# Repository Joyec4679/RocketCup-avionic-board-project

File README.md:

# 🚀 RocketCup Avionic Board Project (成大 ISP 航電組)

歡迎來到成大 ISP 航電組的協作平台！這裡存放了我們為比賽設計的所有電路圖與 PCB 檔案。

因為大家都是第一次使用 GitHub，請**務必**仔細閱讀以下的操作指南，以避免檔案衝突或覆蓋掉別人的心血。

---

## 📂 檔案結構說明 (去哪裡找你的檔案？)

我們採用分工合作的資料夾結構，請在自己的負責區域內工作：

* **`BigAvionic/`**: 大火箭航電板專區
* **`SmallAvionic/`**: 小火箭航電板專區
* **`Lib/`**: 共用的零件庫 (Symbol & Footprint)

> ⚠️ **重要原則**：除非你要修改共用零件庫，否則請盡量專注在自己負責的資料夾內，避免動到別組的檔案。

---

## ⚡ 每日開發流程 (SOP)

為了避免「悲劇」（檔案衝突），請大家養成習慣，每次開工前都要唸一遍口訣：**「先拉，再做，後推」**。

### 1️⃣ 開工第一件事：拉取 (Pull)
**只要你剛坐下準備開始畫圖，不管你覺得有沒有人改過，請先執行：**
```bash
git pull origin main

```

* **為什麼？** 這是把雲端最新的進度同步到你的電腦。如果你不拉就開始改，最後上傳時會發生衝突。

### 2️⃣ 進行開發

* 打開 KiCad，編輯你的電路圖或 PCB。
* 記得隨時存檔 (Ctrl+S)。

### 3️⃣ 收工上傳三步曲：加、存、推

當你完成一個階段的工作（例如：畫完電源線、放完電容），請依序執行：

**Step A: 加入變更 (Add)**
告訴 Git 這一輪你要上傳哪些檔案。

```bash
git add .

```

**Step B: 提交紀錄 (Commit)**
寫下你到底改了什麼。
！！！絕對不要有啥都沒有描述的commit！！！

```bash
git commit -m "清楚的描述，例如：完成 RocketCom 的 3.3V 電源佈線"

```

**Step C: 推送到雲端 (Push)**
這一步才是真的傳到 GitHub 上。

```bash
git push origin main

```

---

## 💣 KiCad 協作特別注意事項 (必讀！)

### 1. 關於 PCB 檔案 (`.kicad_pcb`)

Git 很擅長合併程式碼，但**非常不擅長合併 PCB 檔**。

* **黃金法則**：同一時間，**只能有一個人**修改同一張 PCB 板。
* **溝通**：要改 Layout 之前，請在群組喊一聲：「我要改通訊板的 PCB 囉！」，確認沒人正在改再動手。

---

## ❓ 常見問題救生圈

### Q1: 我輸入 `git push` 時出現 `error: failed to push some refs...` 怎麼辦？

這代表有人在你工作的時候，已經先上傳了新版本。
**解法：**

1. 先輸入 `git pull origin main` (把對方的東西抓下來合併)。
2. 如果不幸出現衝突 (Conflict)，請找組長求救。
3. 合併成功後，再輸入一次 `git push origin main`。

### Q2: 為什麼有些備份檔 (`.bak`) 傳不上去？

這是正常的！我們設定了 `.gitignore` 來過濾掉那些垃圾檔案，保持專案乾淨。請不要強行上傳它們。

---

### 🔧 環境設定檢查

* **KiCad 版本**：請大家統一使用 **KiCad 7.0** ，避免檔案格式跑掉。
* **Git 設定**：第一次使用請設定你的名字和 Email：
```bash
git config --global user.name "你的名字(英文)"
git config --global user.email "你的Email"
```

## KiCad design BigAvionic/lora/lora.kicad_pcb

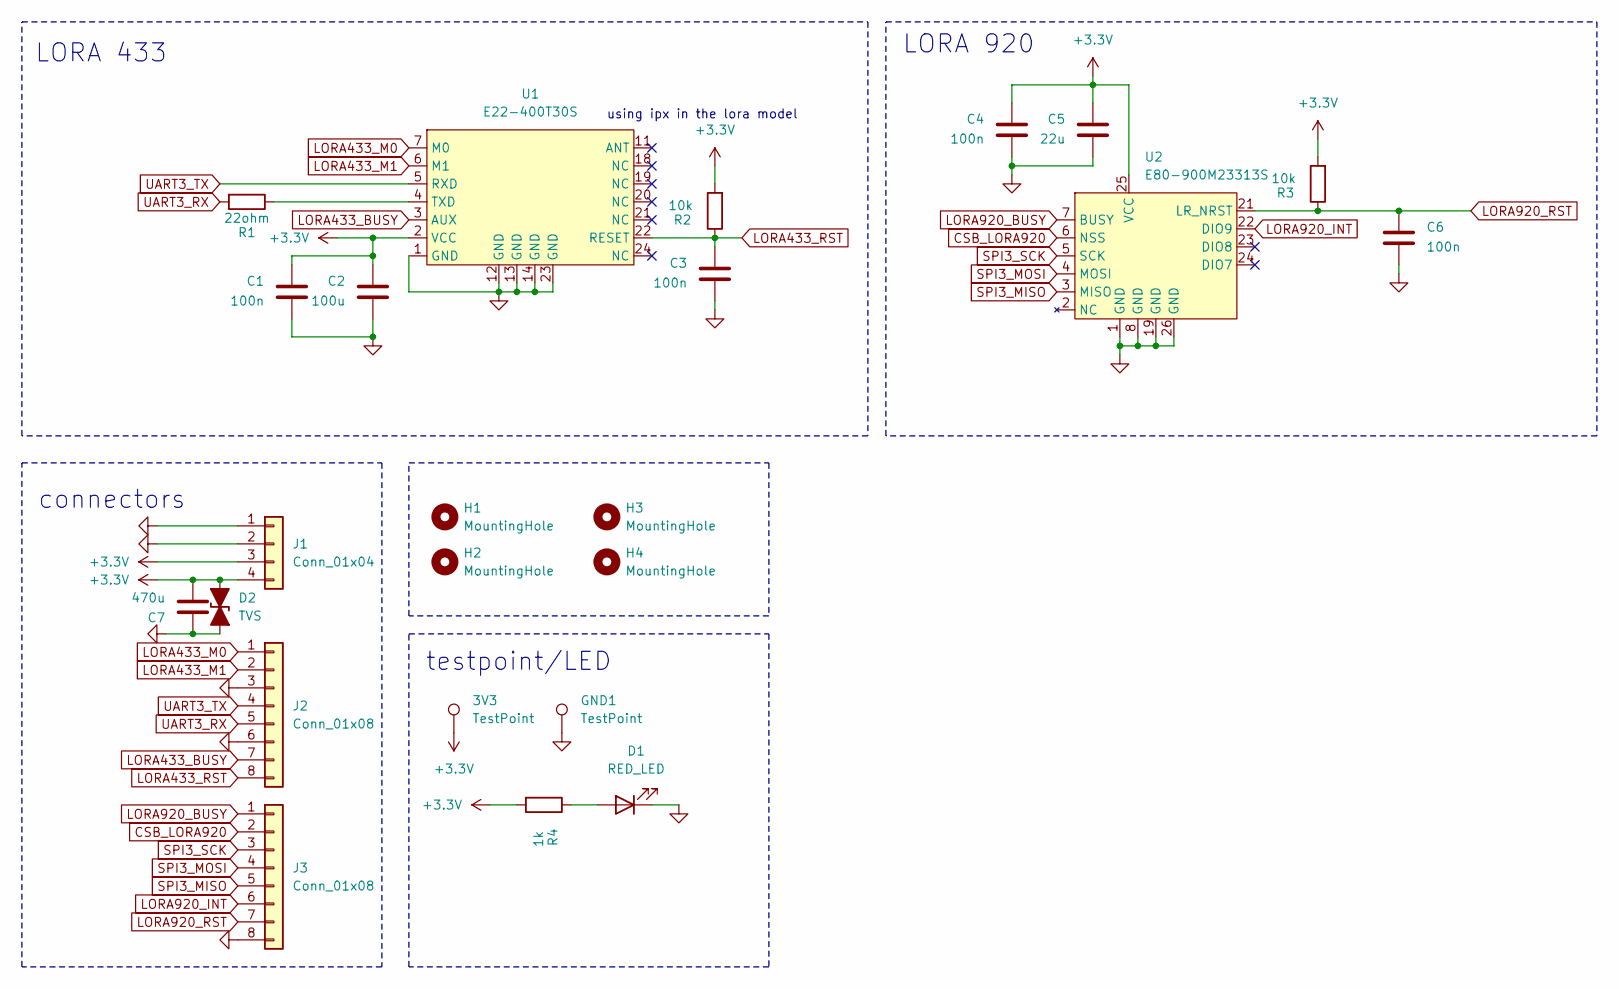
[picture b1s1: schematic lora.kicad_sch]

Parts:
3V3: TestPoint; TestPoint_Pad_D1.0mm
C1, C3, C4, C6: 100n; C_0805_2012Metric_Pad1.18x1.45mm_HandSolder
C2: 100u; CP_EIA-7343-31_Kemet-D_HandSolder
C5: 22u; C_1206_3216Metric_Pad1.33x1.80mm_HandSolder
C7: 470u; CP_EIA-7343-43_Kemet-X_HandSolder
D1: RED_LED; LED_0805_2012Metric_Pad1.15x1.40mm_HandSolder
D2: TVS; D_SMA
GND1: TestPoint; TestPoint_Pad_D1.0mm
H1, H2, H3, H4: MountingHole; MountingHole_3.2mm_M3_DIN965_Pad
J1: Conn_01x04; JST_GH_SM04B-GHS-TB_1x04-1MP_P1.25mm_Horizontal
J2, J3: Conn_01x08; JST_GH_SM08B-GHS-TB_1x08-1MP_P1.25mm_Horizontal
R1: 22ohm; R_0805_2012Metric_Pad1.20x1.40mm_HandSolder
R2, R3: 10k; R_0805_2012Metric_Pad1.20x1.40mm_HandSolder
R4: 1k; R_0805_2012Metric_Pad1.20x1.40mm_HandSolder
U1: E22-400T30S; XCVR_E22-900T30S
U2: E80-900M23313S; E80-xxxM2213S

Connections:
+3.3V: 3V3.1, C1.1, C2.1, C4.1, C5.1, C7.2, D2.2 (A2), J1.3, J1.4, R2.2, R3.2, R4.2, U1.2 (VCC), U2.25 (VCC)
CSB_LORA920: J3.2, U2.6 (NSS)
GND: C1.2, C2.2, C3.2, C4.2, C5.2, C6.2, C7.1, D1.1 (K), D2.1 (A1), GND1.1, J1.1, J1.2, J2.3, J2.6, J3.8, U1.1 (GND), U1.12 (GND), U1.13 (GND), U1.14 (GND), U1.23 (GND), U2.1 (GND), U2.8 (GND), U2.19 (GND), U2.26 (GND)
LORA433_BUSY: J2.7, U1.3 (AUX)
LORA433_M0: J2.1, U1.7 (M0)
LORA433_M1: J2.2, U1.6 (M1)
LORA433_RST: C3.1, J2.8, R2.1, U1.22 (RESET)
LORA920_BUSY: J3.1, U2.7 (BUSY)
LORA920_INT: J3.6, U2.22 (DIO9)
LORA920_RST: C6.1, J3.7, R3.1, U2.21 (LR_NRST)
unnamed: D1.2 (A), R4.1
unnamed: R1.1, U1.4 (TXD)
SPI3_MISO: J3.5, U2.3 (MISO)
SPI3_MOSI: J3.4, U2.4 (MOSI)
SPI3_SCK: J3.3, U2.5 (SCK)
UART3_RX: J2.5, R1.2
UART3_TX: J2.4, U1.5 (RXD)

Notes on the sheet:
LORA 920
testpoint/LED
using ipx in the lora model
connectors
LORA 433

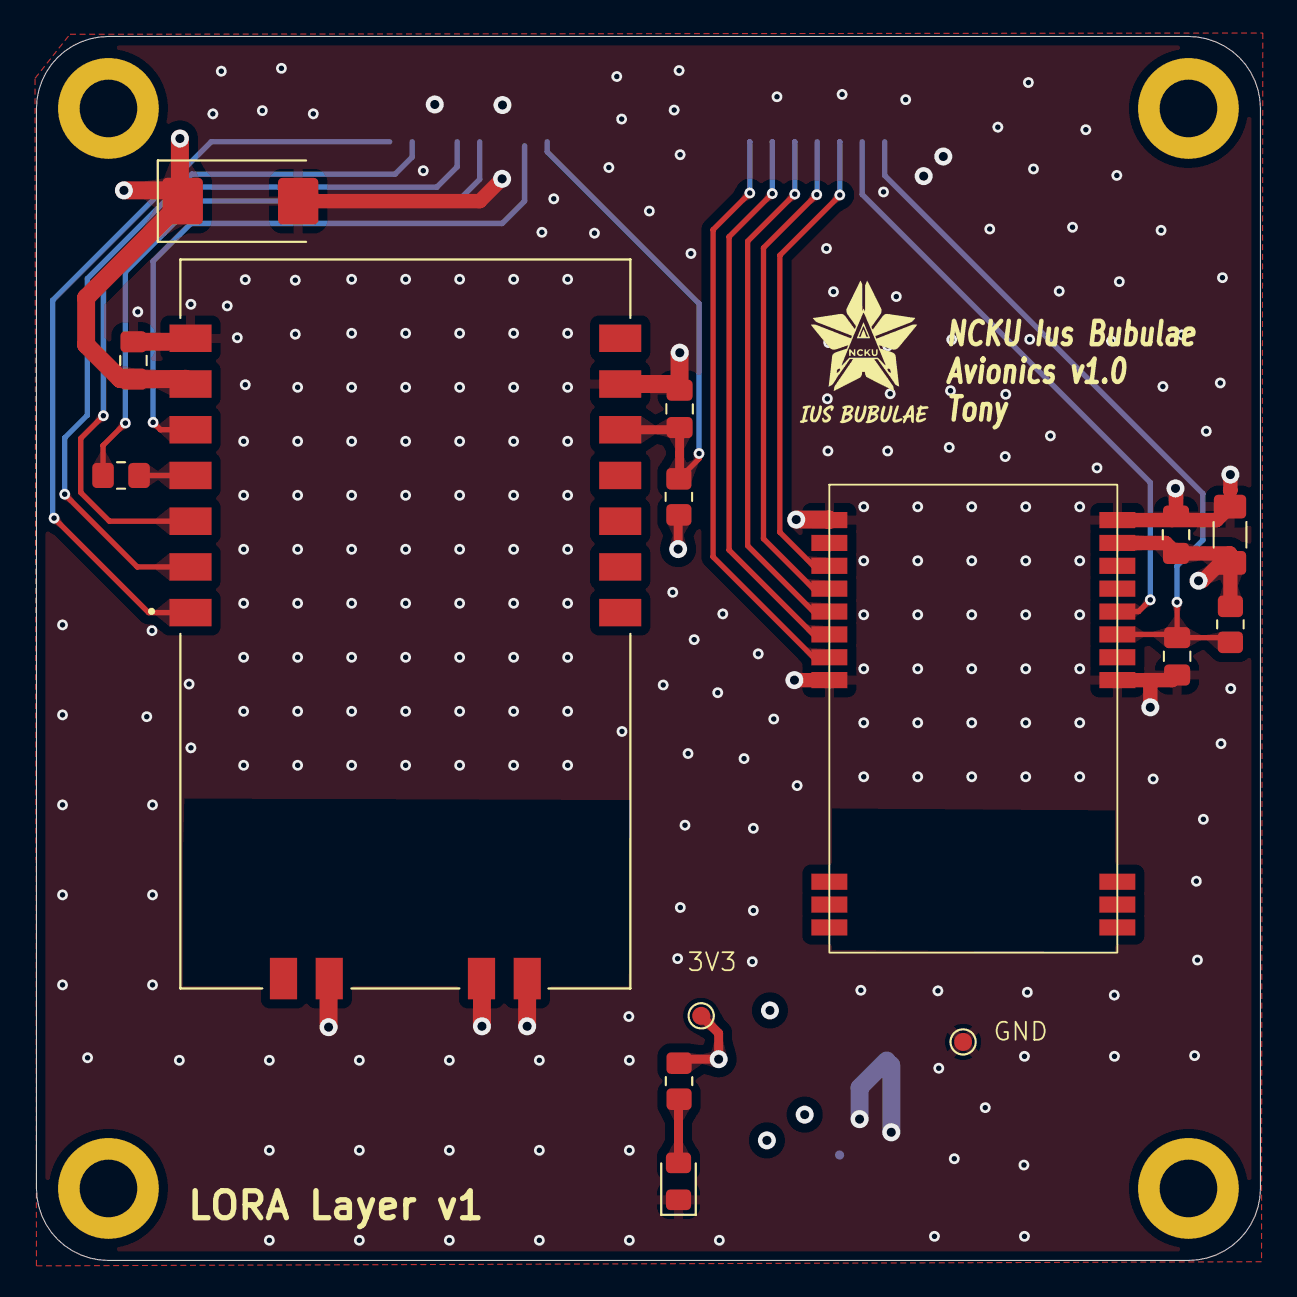
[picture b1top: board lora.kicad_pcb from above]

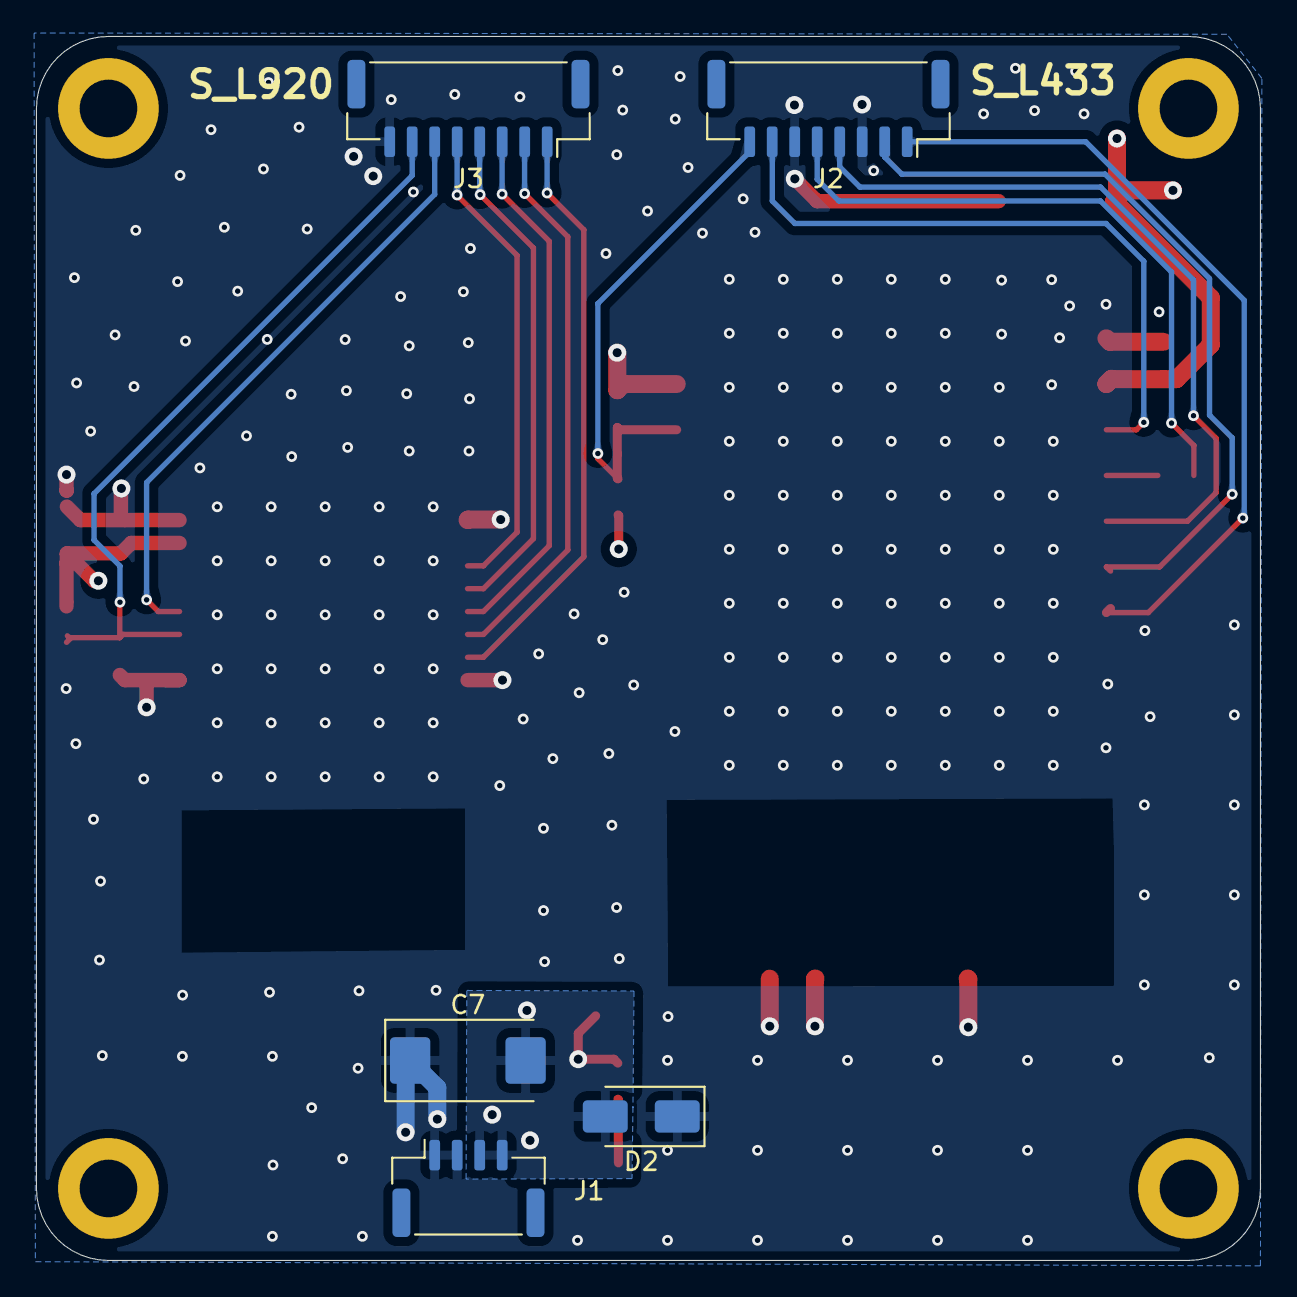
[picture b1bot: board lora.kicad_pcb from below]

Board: 4 copper layers, 68.0 x 68.0 mm, 24 parts (5 on the bottom side), 17 nets.

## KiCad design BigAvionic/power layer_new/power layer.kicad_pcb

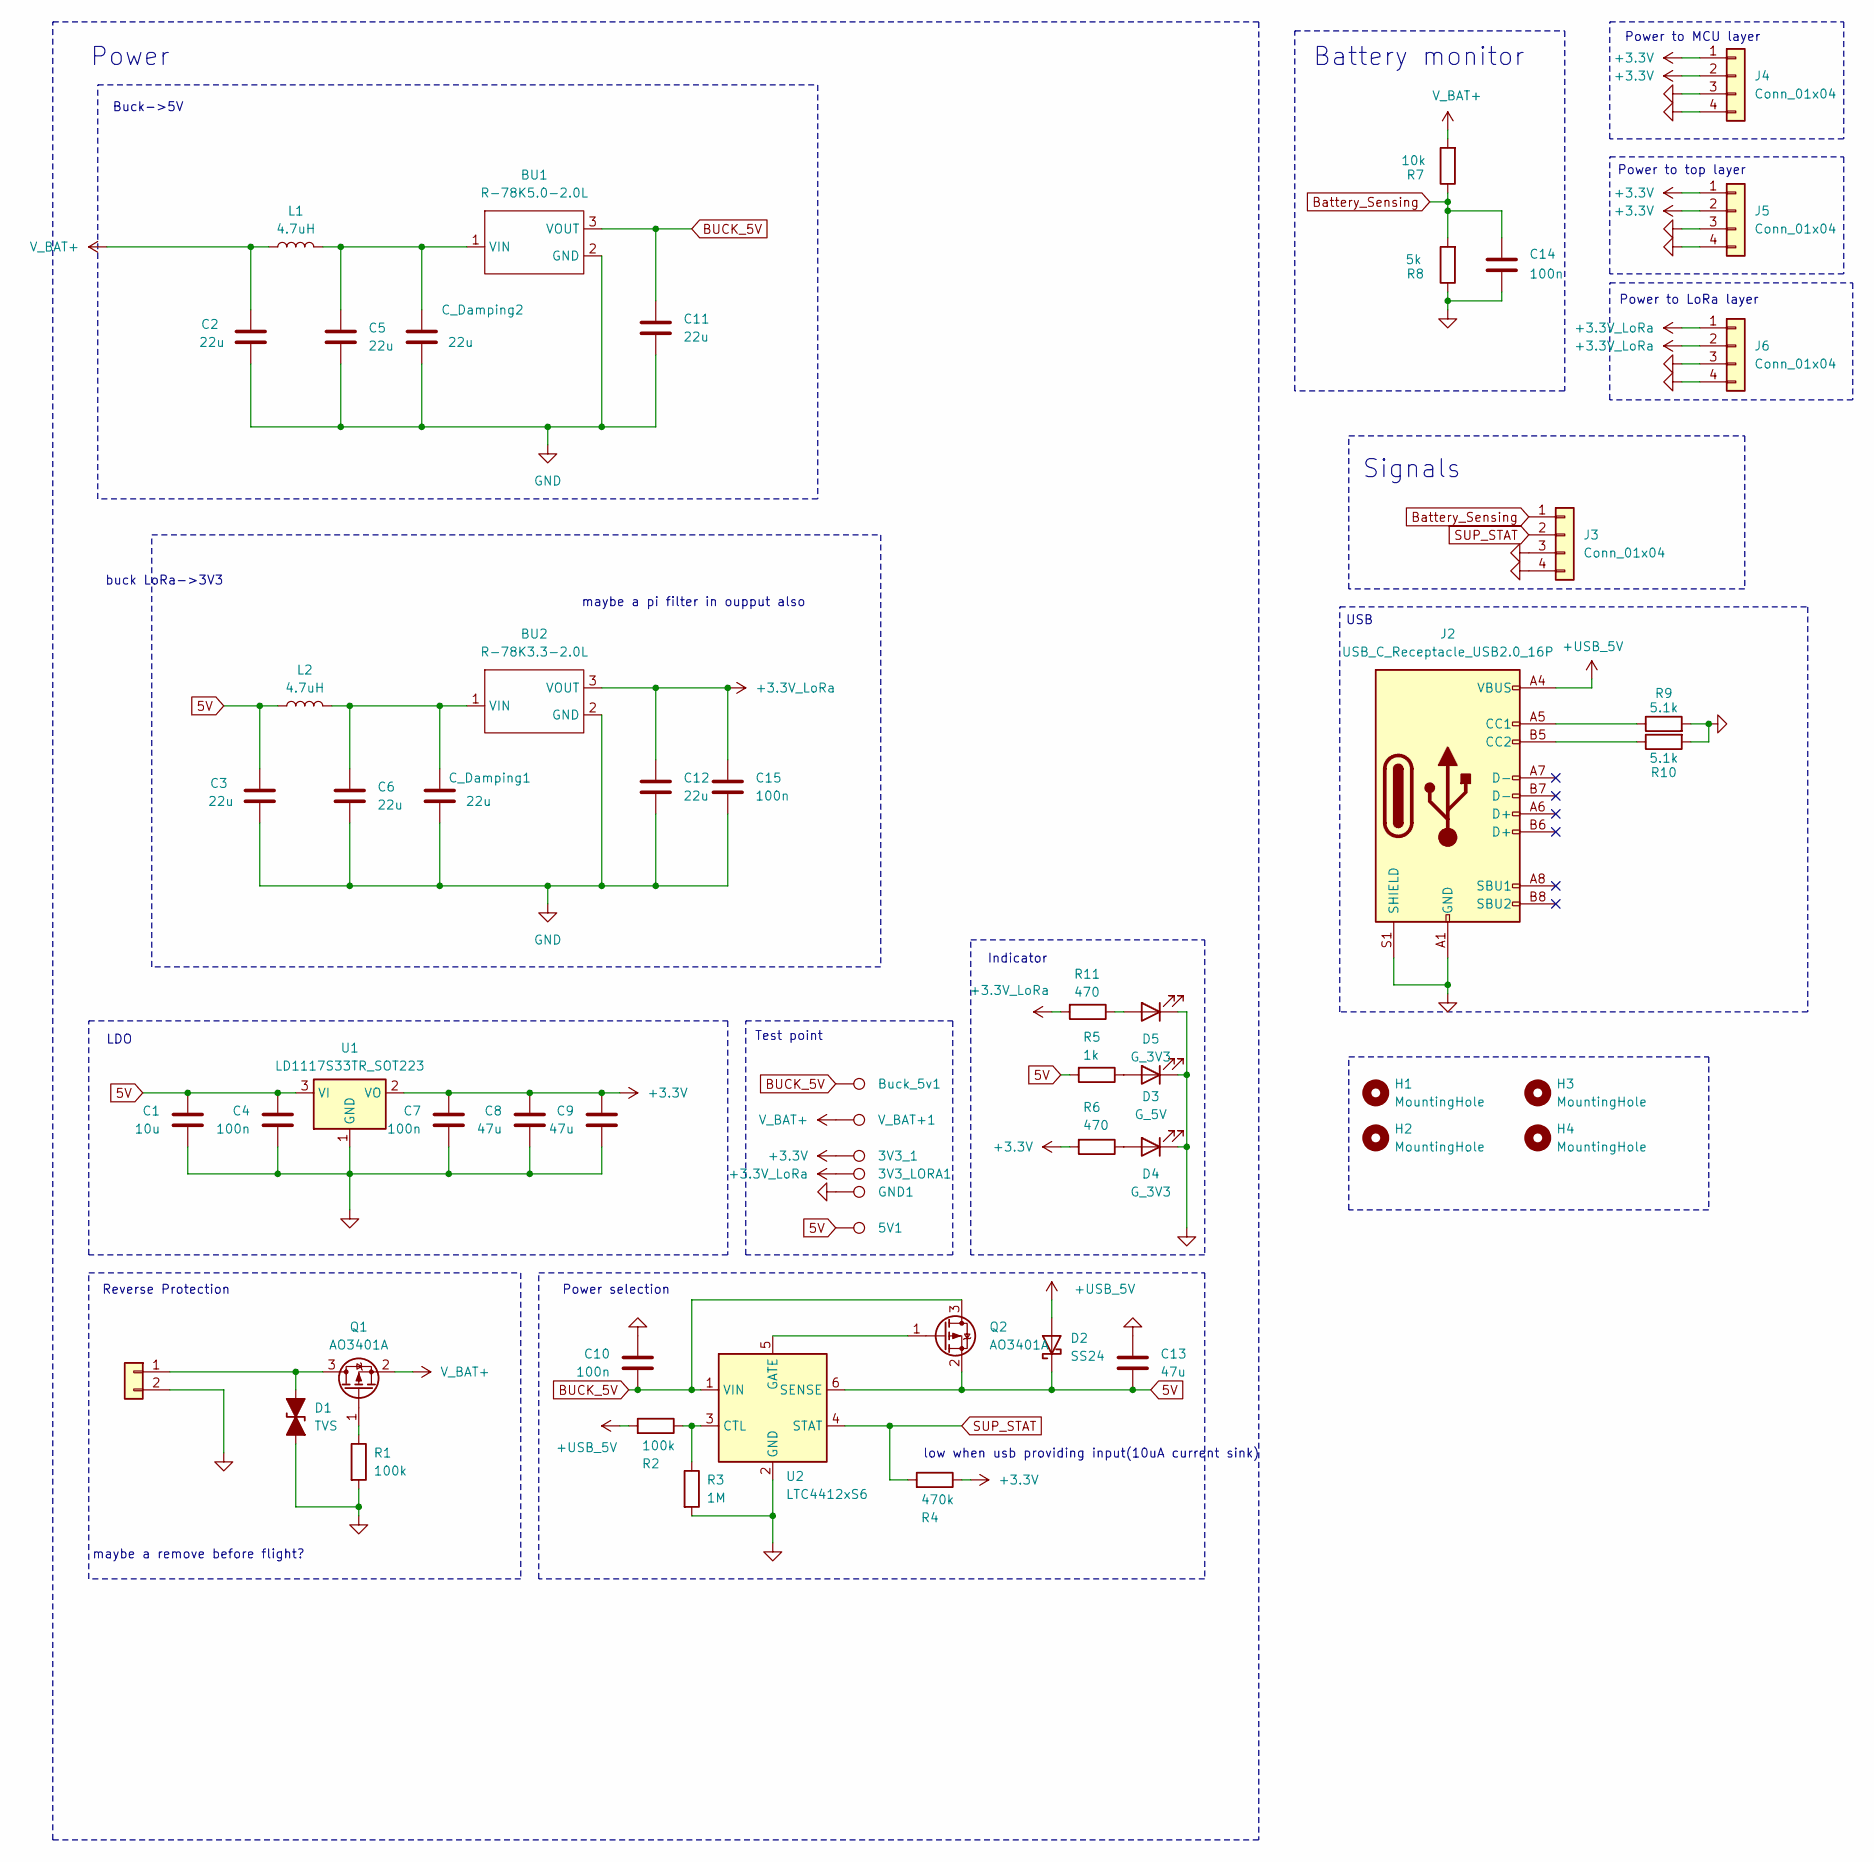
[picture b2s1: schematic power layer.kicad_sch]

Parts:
3V3_1, 3V3_LORA1, 5V1: TestPoint; TestPoint_Pad_D1.0mm
BU1: R-78K5.0-2.0L; CONV_R-78K5.0-2.0L
BU2: R-78K3.3-2.0L; CONV_R-78K5.0-2.0L
Buck_5v1: TestPoint; TestPoint_Pad_D1.0mm
C1: 10u; C_1210_3225Metric_Pad1.33x2.70mm_HandSolder
C2, C3, C5, C6, C11, C12: 22u; C_1210_3225Metric_Pad1.33x2.70mm_HandSolder
C4, C7, C10, C14, C15: 100n; C_0805_2012Metric_Pad1.18x1.45mm_HandSolder
C8, C9, C13: 47u; C_1210_3225Metric_Pad1.33x2.70mm_HandSolder
C_Damping1, C_Damping2: 22u; CP_EIA-3528-21_Kemet-B_HandSolder
D1: TVS; D_SMA
D2: SS24; D_SMA
D3: G_5V; LED_0805_2012Metric_Pad1.15x1.40mm_HandSolder
D4, D5: G_3V3; LED_0805_2012Metric_Pad1.15x1.40mm_HandSolder
GND1: TestPoint; TestPoint_Pad_D1.0mm
H1, H2, H3, H4: MountingHole; MountingHole_3.2mm_M3_DIN965_Pad
J1: Conn_01x02; JST_PH_S2B-PH-K_1x02_P2.00mm_Horizontal
J2: USB_C_Receptacle_USB2.0_16P; USB_C_Receptacle_HRO_TYPE-C-31-M-12
J3, J4, J5, J6: Conn_01x04; JST_GH_SM04B-GHS-TB_1x04-1MP_P1.25mm_Horizontal
L1, L2: 4.7uH; L_APV_ANR4020
Q1, Q2: AO3401A; SOT-23
R1, R2: 100k; R_0805_2012Metric_Pad1.20x1.40mm_HandSolder
R3: 1M; R_0805_2012Metric_Pad1.20x1.40mm_HandSolder
R4: 470k; R_0805_2012Metric_Pad1.20x1.40mm_HandSolder
R5: 1k; R_0805_2012Metric_Pad1.20x1.40mm_HandSolder
R6, R11: 470; R_0805_2012Metric_Pad1.20x1.40mm_HandSolder
R7: 10k; R_0805_2012Metric_Pad1.20x1.40mm_HandSolder
R8: 5k; R_0805_2012Metric_Pad1.20x1.40mm_HandSolder
R9, R10: 5.1k; R_0805_2012Metric_Pad1.20x1.40mm_HandSolder
U1: LD1117S33TR_SOT223; SOT-223-3_TabPin2
U2: LTC4412xS6; TSOT-23-6
V_BAT+1: TestPoint; TestPoint_Pad_D1.0mm

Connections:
5V: 5V1.1, C1.1, C3.1, C4.1, C13.2, D2.1 (K), L2.1, Q2.2 (S), R5.2, U1.3 (VI), U2.6 (SENSE)
+3.3V: 3V3_1.1, C7.1, C8.1, C9.1, J4.1, J4.2, J5.1, J5.2, R4.1, R6.2, U1.2 (VO)
+3.3V_LoRa: 3V3_LORA1.1, BU2.3 (VOUT), C12.1, C15.1, J6.1, J6.2, R11.2
+USB_5V: D2.2 (A), J2.A4 (VBUS), J2.A9 (VBUS), J2.B4 (VBUS), J2.B9 (VBUS), R2.2
BUCK_5V: BU1.3 (VOUT), Buck_5v1.1, C10.2, C11.1, Q2.3 (D), U2.1 (VIN)
Battery_Sensing: C14.1, J3.1, R7.1, R8.2
GND: BU1.2 (GND), BU2.2 (GND), C1.2, C2.2, C3.2, C4.2, C5.2, C6.2, C7.2, C8.2, C9.2, C10.1, C11.2, C12.2, C13.1, C14.2, C15.2, C_Damping1.2, C_Damping2.2, D1.1 (A1), D3.1 (K), D4.1 (K), D5.1 (K), GND1.1, J1.2, J2.A1 (GND), J2.A12 (GND), J2.B1 (GND), J2.B12 (GND), J2.S1 (SHIELD), J3.3, J3.4, J4.3, J4.4, J5.3, J5.4, J6.3, J6.4, R1.2, R3.2, R8.1, R9.2, R10.2, U1.1 (GND), U2.2 (GND)
unnamed: BU1.1 (VIN), C5.1, C_Damping2.1, L1.2
unnamed: BU2.1 (VIN), C6.1, C_Damping1.1, L2.2
unnamed: D1.2 (A2), J1.1, Q1.3 (D)
unnamed: D3.2 (A), R5.1
unnamed: D4.2 (A), R6.1
unnamed: D5.2 (A), R11.1
unnamed: J2.A5 (CC1), R9.1
unnamed: J2.B5 (CC2), R10.1
unnamed: Q1.1 (G), R1.1
unnamed: Q2.1 (G), U2.5 (GATE)
unnamed: R2.1, R3.1, U2.3 (CTL)
SUP_STAT: J3.2, R4.2, U2.4 (STAT)
V_BAT+: C2.1, L1.1, Q1.2 (S), R7.2, V_BAT+1.1

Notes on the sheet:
LDO
Indicator
maybe a pi filter in oupput also
Power selection
USB
Buck->5V
maybe a remove before flight?
buck LoRa->3V3
Power to MCU layer
Signals
Reverse Protection
Test point
low when usb providing input(10uA current sink)
Battery monitor
Power
Power to top layer
Power to LoRa layer

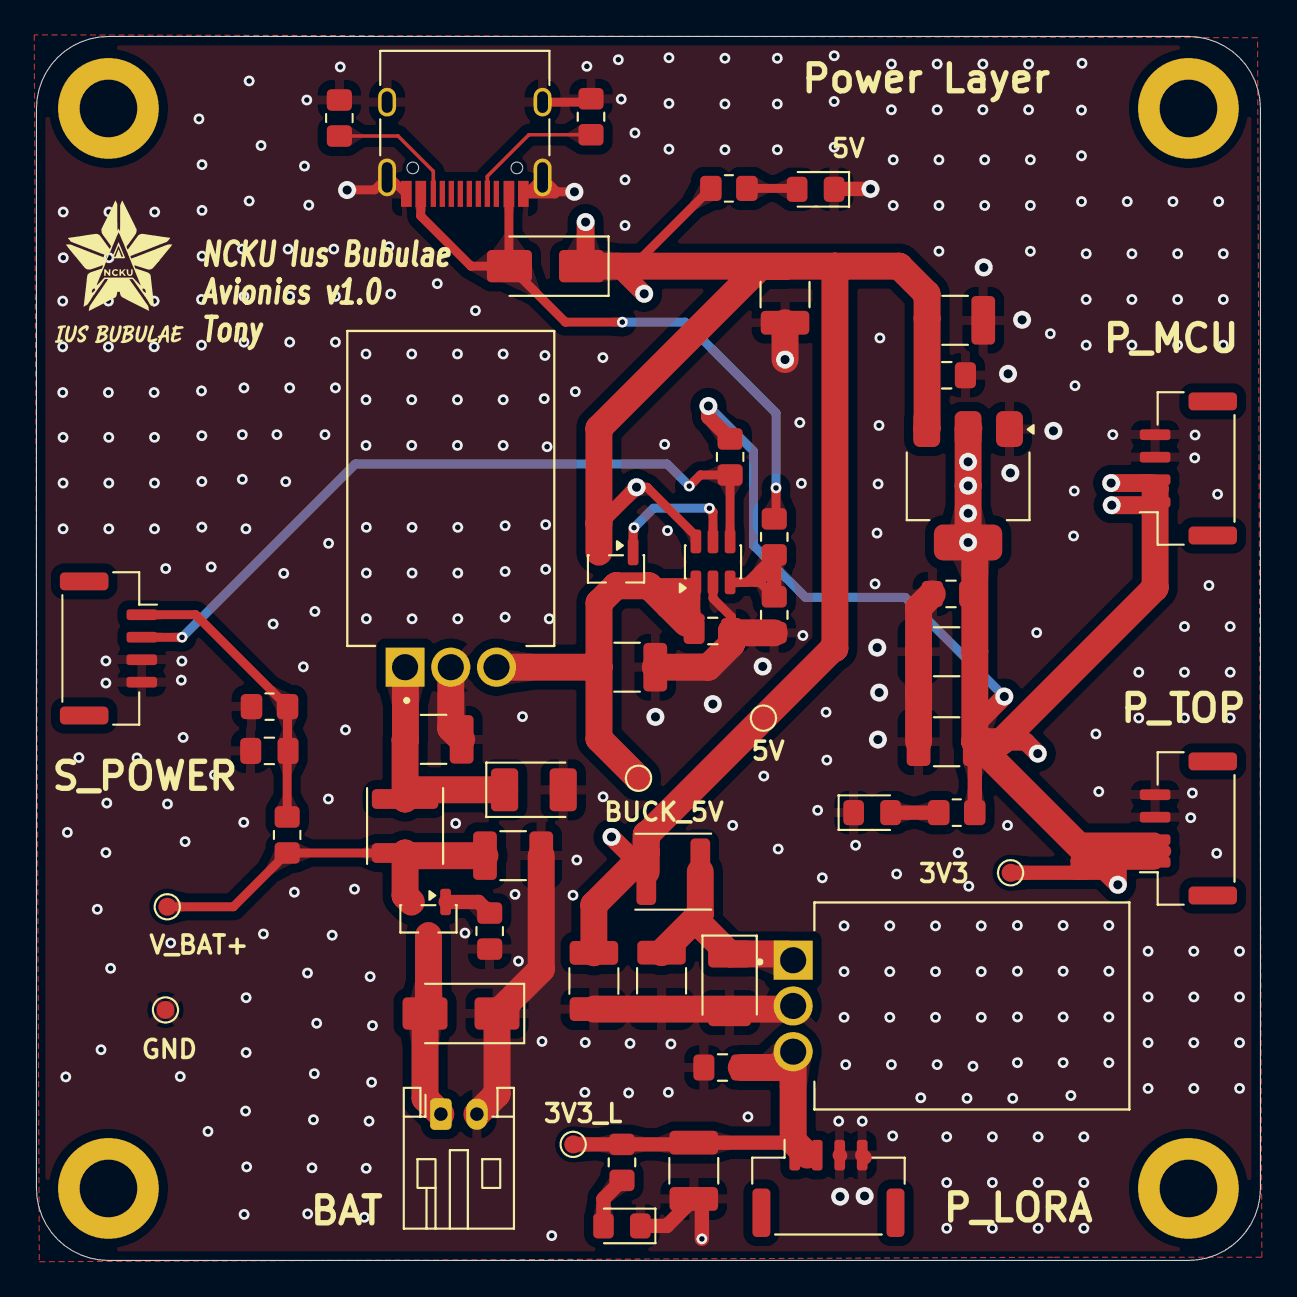
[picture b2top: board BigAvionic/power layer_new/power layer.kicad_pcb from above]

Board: 4 copper layers, 68.0 x 68.0 mm, 57 parts (0 on the bottom side), 20 nets.

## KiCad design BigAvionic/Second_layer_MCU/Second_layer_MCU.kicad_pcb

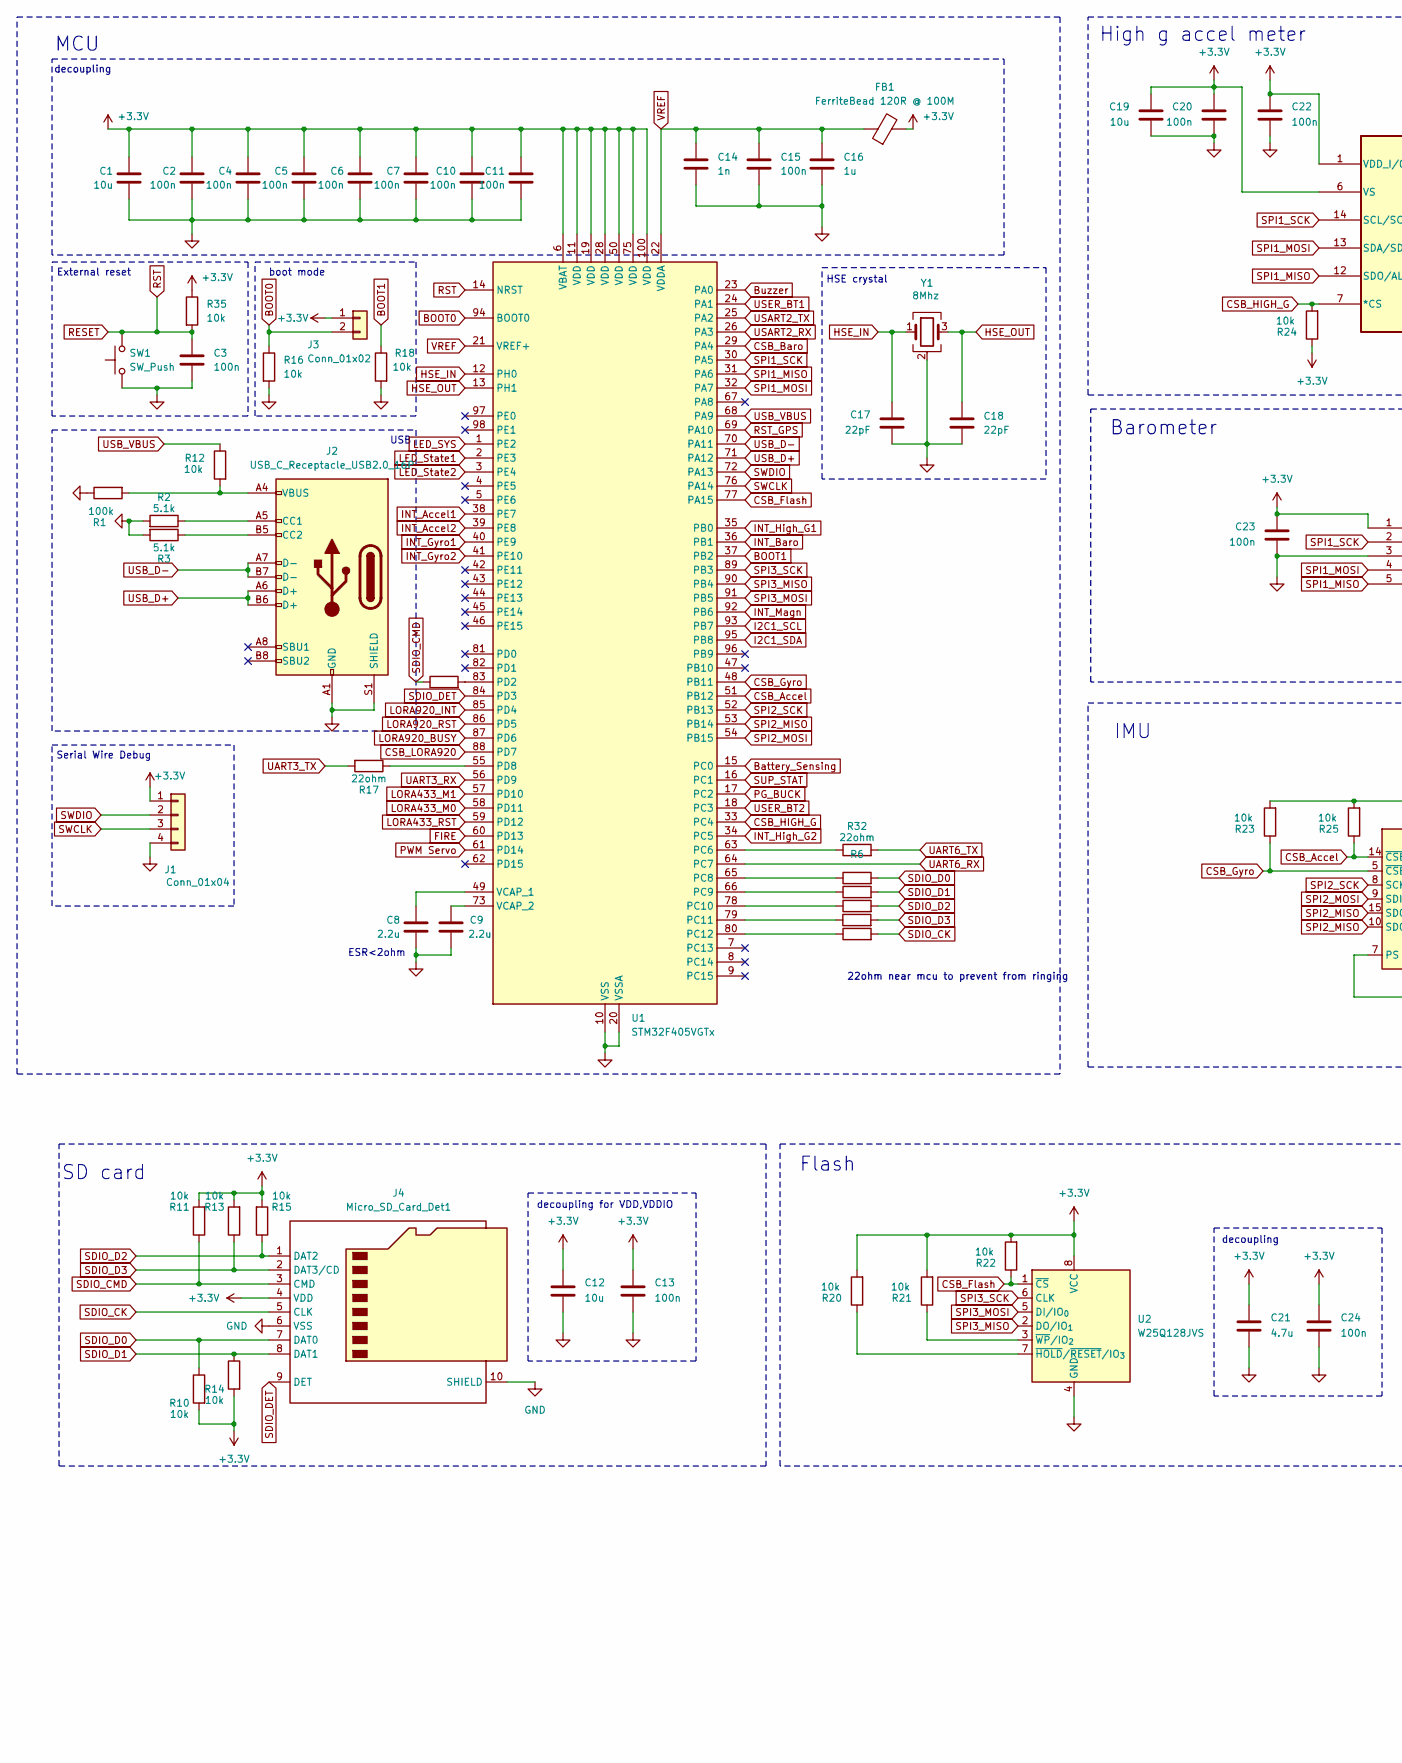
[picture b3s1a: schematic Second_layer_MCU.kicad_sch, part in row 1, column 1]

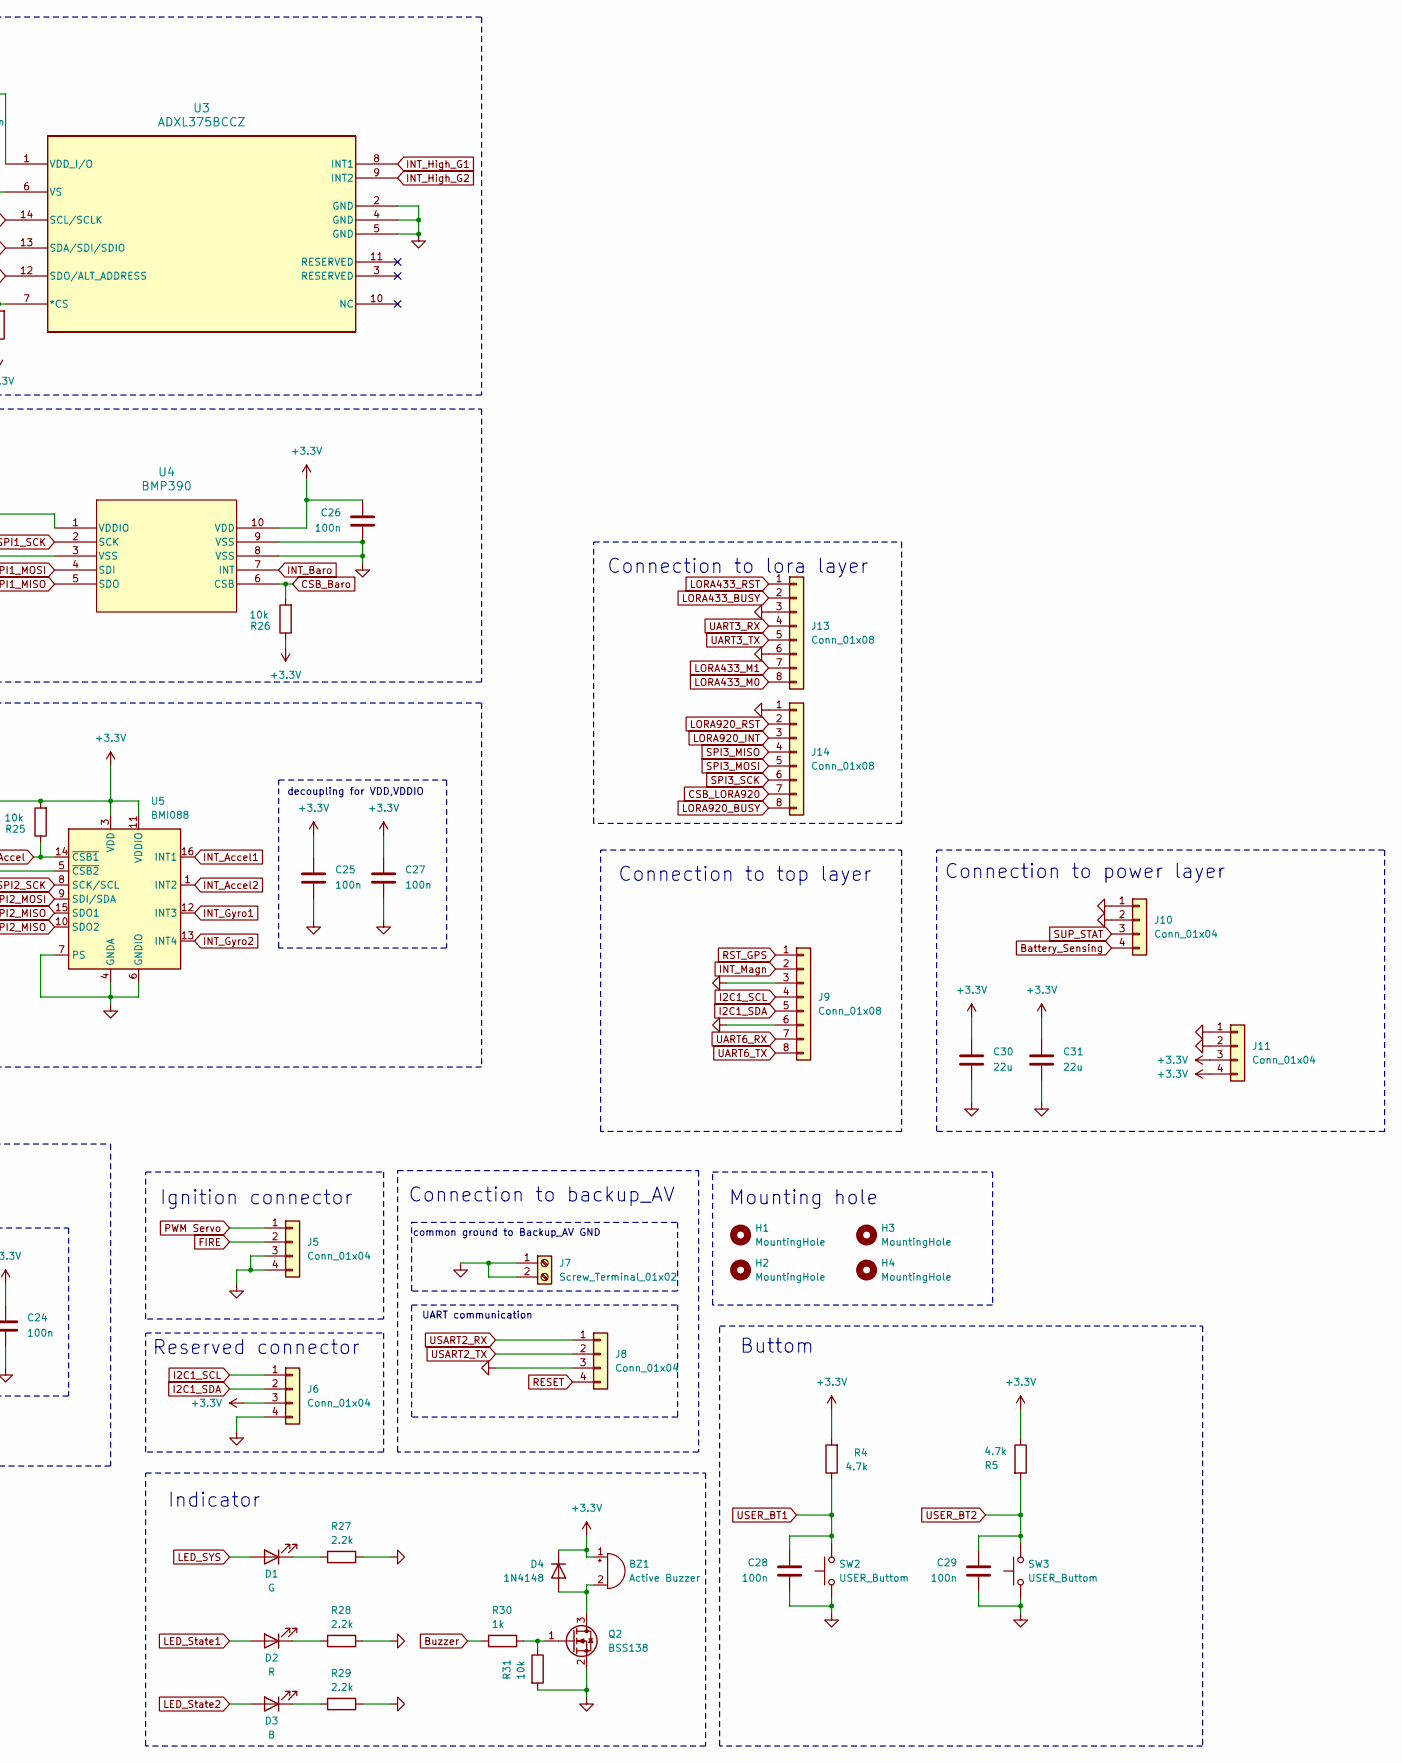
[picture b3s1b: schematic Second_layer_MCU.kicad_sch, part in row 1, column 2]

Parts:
BZ1: Active Buzzer; MagneticBuzzer_CUI_CMT-8504-100-SMT
C1, C12, C19: 10u; C_0805_2012Metric_Pad1.18x1.45mm_HandSolder
C2, C3, C4, C5, C6, C7, C10, C11, C13, C15, C20, C22, C23, C24, C25, C26, C27, C28, C29: 100n; C_0402_1005Metric_Pad0.74x0.62mm_HandSolder
C8, C9: 2.2u; C_0603_1608Metric_Pad1.08x0.95mm_HandSolder
C14: 1n; C_0402_1005Metric_Pad0.74x0.62mm_HandSolder
C16: 1u; C_0402_1005Metric_Pad0.74x0.62mm_HandSolder
C17, C18: 22pF; C_0603_1608Metric_Pad1.08x0.95mm_HandSolder
C21: 4.7u; C_0805_2012Metric_Pad1.18x1.45mm_HandSolder
C30, C31: 22u; C_1206_3216Metric_Pad1.33x1.80mm_HandSolder
D1: G; LED_0805_2012Metric_Pad1.15x1.40mm_HandSolder
D2: R; LED_0805_2012Metric_Pad1.15x1.40mm_HandSolder
D3: B; LED_0805_2012Metric_Pad1.15x1.40mm_HandSolder
D4: 1N4148; D_SOD-123
FB1: FerriteBead 120R @ 100M; L_0805_2012Metric_Pad1.05x1.20mm_HandSolder
H1, H2, H3, H4: MountingHole; MountingHole_3.2mm_M3_DIN965_Pad
J1, J6: Conn_01x04; PinHeader_1x04_P2.54mm_Vertical
J2: USB_C_Receptacle_USB2.0_16P; USB_C_Receptacle_HRO_TYPE-C-31-M-12
J3: Conn_01x02; PinHeader_1x02_P2.54mm_Vertical
J4: Micro_SD_Card_Det1; microSD_HC_Molex_104031-0811
J5, J8, J10, J11: Conn_01x04; JST_GH_SM04B-GHS-TB_1x04-1MP_P1.25mm_Horizontal
J7: Screw_Terminal_01x02; TerminalBlock_Phoenix_PT-1,5-2-3.5-H_1x02_P3.50mm_Horizontal
J9, J13, J14: Conn_01x08; JST_GH_SM08B-GHS-TB_1x08-1MP_P1.25mm_Horizontal
Q2: BSS138; SOT-23
R1: 100k; R_0402_1005Metric_Pad0.72x0.64mm_HandSolder
R2, R3: 5.1k; R_0402_1005Metric_Pad0.72x0.64mm_HandSolder
R4, R5: 4.7k; R_0402_1005Metric_Pad0.72x0.64mm_HandSolder
R6, R7, R8, R9, R17, R19, R32, R33: 22ohm; R_0402_1005Metric_Pad0.72x0.64mm_HandSolder
R10, R11, R12, R13, R14, R15, R16, R18, R20, R21, R22, R23, R24, R25, R26, R31, R35: 10k; R_0402_1005Metric_Pad0.72x0.64mm_HandSolder
R27, R28, R29: 2.2k; R_0402_1005Metric_Pad0.72x0.64mm_HandSolder
R30: 1k; R_0402_1005Metric_Pad0.72x0.64mm_HandSolder
SW1: SW_Push; SW_PUSH_6mm_H4.3mm
SW2, SW3: USER_Buttom; SW_PUSH_6mm_H4.3mm
U1: STM32F405VGTx; LQFP-100_14x14mm_P0.5mm
U2: W25Q128JVS; SOIC-8_5.3x5.3mm_P1.27mm
U3: ADXL375BCCZ; LGA_CC-14-1_ADI-L
U4: BMP390; 10LGA_2X2X0p75_BOS-M
U5: BMI088; Bosch_LGA-16_4.5x3mm_P0.5mm_LayoutBorder7x1y_ClockwisePinNu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
Y1: 8Mhz; Crystal_SMD_3225-4Pin_3.2x2.5mm_HandSoldering

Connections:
+3.3V: BZ1.1 (+), C1.1, C2.1, C4.1, C5.1, C6.1, C7.1, C10.1, C11.1, C12.1, C13.1, C19.1, C20.1, C21.1, C22.1, C23.1, C24.1, C25.1, C26.1, C27.1, C30.1, C31.1, D4.1 (K), FB1.2, J1.1, J3.1, J4.4 (VDD), J6.3, J11.3, J11.4, R4.2, R5.1, R10.2, R11.2, R13.2, R14.2, R15.2, R20.2, R21.2, R22.2, R23.2, R24.1, R25.2, R26.1, R35.1, U1.6 (VBAT), U1.11 (VDD), U1.19 (VDD), U1.28 (VDD), U1.50 (VDD), U1.75 (VDD), U1.100 (VDD), U2.8 (VCC), U3.1 (VDD_I/O), U3.6 (VS), U4.1 (VDDIO), U4.10 (VDD), U5.3 (VDD), U5.11 (VDDIO)
BOOT0: J3.2, R16.1, U1.94 (BOOT0)
BOOT1: R18.1, U1.37 (PB2)
Battery_Sensing: J10.4, U1.15 (PC0)
Buzzer: R30.2, U1.23 (PA0)
CSB_Accel: R25.1, U1.51 (PB12), U5.14 (~CSB1)
CSB_Baro: R26.2, U1.29 (PA4), U4.6 (CSB)
CSB_Flash: R22.1, U1.77 (PA15), U2.1 (~CS)
CSB_Gyro: R23.1, U1.48 (PB11), U5.5 (~CSB2)
CSB_HIGH_G: R24.2, U1.33 (PC4), U3.7 (*CS)
CSB_LORA920: J14.7, U1.88 (PD7)
FIRE: J5.2, U1.60 (PD13)
GND: C1.2, C2.2, C3.2, C4.2, C5.2, C6.2, C7.2, C8.2, C9.2, C10.2, C11.2, C12.2, C13.2, C14.2, C15.2, C16.2, C17.2, C18.2, C19.2, C20.2, C21.2, C22.2, C23.2, C24.2, C25.2, C26.2, C27.2, C28.2, C29.2, C30.2, C31.2, J1.4, J2.A1 (GND), J2.A12 (GND), J2.B1 (GND), J2.B12 (GND), J2.S1 (SHIELD), J4.6 (VSS), J4.10 (SHIELD), J5.3, J5.4, J6.4, J7.1, J7.2, J8.3, J9.3, J9.6, J10.1, J10.2, J11.1, J11.2, J13.3, J13.6, J14.1, Q2.2 (S), R1.1, R2.2, R3.2, R16.2, R18.2, R27.1, R28.1, R29.1, R31.2, SW1.1, SW2.1, SW2.SH (B), SW3.1, SW3.SH (B), U1.10 (VSS), U1.20 (VSSA), U1.27 (VSS), U1.74 (VSS), U1.99 (VSS), U2.4 (GND), U3.2 (GND), U3.4 (GND), U3.5 (GND), U4.3 (VSS), U4.8 (VSS), U4.9 (VSS), U5.2 (GNDA), U5.4 (GNDA), U5.6 (GNDIO), U5.7 (PS), Y1.2 (G), Y1.4 (G)
HSE_IN: C17.1, U1.12 (PH0), Y1.1
HSE_OUT: C18.1, U1.13 (PH1), Y1.3
I2C1_SCL: J6.1, J9.4, U1.93 (PB7)
I2C1_SDA: J6.2, J9.5, U1.95 (PB8)
INT_Accel1: U1.38 (PE7), U5.16 (INT1)
INT_Accel2: U1.39 (PE8), U5.1 (INT2)
INT_Baro: U1.36 (PB1), U4.7 (INT)
INT_Gyro1: U1.40 (PE9), U5.12 (INT3)
INT_Gyro2: U1.41 (PE10), U5.13 (INT4)
INT_High_G1: U1.35 (PB0), U3.8 (INT1)
INT_High_G2: U1.34 (PC5), U3.9 (INT2)
INT_Magn: J9.2, U1.43 (PE12), U1.92 (PB6)
LED_SYS: D1.2 (A), U1.1 (PE2)
LED_State1: D2.2 (A), U1.2 (PE3)
LED_State2: D3.2 (A), U1.3 (PE4)
LORA433_BUSY: J13.2, U1.42 (PE11)
LORA433_M0: J13.8, U1.58 (PD11)
LORA433_M1: J13.7, U1.57 (PD10)
LORA433_RST: J13.1, U1.59 (PD12)
LORA920_BUSY: J14.8, U1.87 (PD6)
LORA920_INT: J14.3, U1.85 (PD4)
LORA920_RST: J14.2, U1.86 (PD5)
unnamed: BZ1.2 (-), D4.2 (A), Q2.3 (D)
unnamed: D1.1 (K), R27.2
unnamed: D2.1 (K), R28.2
unnamed: D3.1 (K), R29.2
unnamed: J2.A5 (CC1), R2.1
unnamed: J2.B5 (CC2), R3.1
unnamed: J2.A4 (VBUS), J2.A9 (VBUS), J2.B4 (VBUS), J2.B9 (VBUS), R1.2, R12.2
unnamed: Q2.1 (G), R30.1, R31.1
unnamed: R32.1, U1.63 (PC6)
unnamed: R6.1, U1.65 (PC8)
unnamed: R7.1, U1.66 (PC9)
unnamed: R8.1, U1.78 (PC10)
unnamed: R9.1, U1.79 (PC11)
unnamed: R19.1, U1.80 (PC12)
unnamed: R33.2, U1.83 (PD2)
unnamed: R17.1, U1.55 (PD8)
unnamed: C8.1, U1.49 (VCAP_1)
unnamed: C9.1, U1.73 (VCAP_2)
unnamed: R20.1, U2.7 (~HOLD/~RESET/IO_{3})
unnamed: R21.1, U2.3 (~WP/IO_{2})
PWM Servo: J5.1, U1.61 (PD14)
RESET: C3.1, J8.4, R35.2, SW1.2, U1.14 (NRST)
RST_GPS: J9.1, U1.67 (PA8), U1.69 (PA10)
SDIO_CK: J4.5 (CLK), R19.2
SDIO_CMD: J4.3 (CMD), R11.1, R33.1
SDIO_D0: J4.7 (DAT0), R6.2, R10.1
SDIO_D1: J4.8 (DAT1), R7.2, R14.1
SDIO_D2: J4.1 (DAT2), R8.2, R15.1
SDIO_D3: J4.2 (DAT3/CD), R9.2, R13.1
SDIO_DET: J4.9 (DET), U1.84 (PD3)
SPI1_MISO: U1.31 (PA6), U3.12 (SDO/ALT_ADDRESS), U4.5 (SDO)
SPI1_MOSI: U1.32 (PA7), U3.13 (SDA/SDI/SDIO), U4.4 (SDI)
SPI1_SCK: U1.30 (PA5), U3.14 (SCL/SCLK), U4.2 (SCK)
SPI2_MISO: U1.53 (PB14), U5.10 (SDO2), U5.15 (SDO1)
SPI2_MOSI: U1.54 (PB15), U5.9 (SDI/SDA)
SPI2_SCK: U1.52 (PB13), U5.8 (SCK/SCL)
SPI3_MISO: J14.4, U1.90 (PB4), U2.2 (DO/IO_{1})
SPI3_MOSI: J14.5, U1.91 (PB5), U2.5 (DI/IO_{0})
SPI3_SCK: J14.6, U1.89 (PB3), U2.6 (CLK)
SUP_STAT: J10.3, U1.16 (PC1)
SWCLK: J1.3, U1.76 (PA14)
SWDIO: J1.2, U1.72 (PA13)
UART3_RX: J13.4, U1.56 (PD9)
UART3_TX: J13.5, R17.2
UART6_RX: J9.7, U1.64 (PC7)
UART6_TX: J9.8, R32.2
USART2_RX: J8.1, U1.26 (PA3)
USART2_TX: J8.2, U1.25 (PA2)
USB_D+: J2.A6 (D+), J2.B6 (D+), U1.71 (PA12)
USB_D-: J2.A7 (D-), J2.B7 (D-), U1.70 (PA11)
USB_VBUS: R12.1, U1.68 (PA9)
USER_BT1: C28.1, R4.1, SW2.2, U1.24 (PA1)
USER_BT2: C29.1, R5.2, SW3.2, U1.18 (PC3)
VREF: C14.1, C15.1, C16.1, FB1.1, U1.21 (VREF+), U1.22 (VDDA)

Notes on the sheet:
Connection to power layer
High g accel meter
HSE crystal
Ignition connector
Connection to top layer
SD card
boot mode
Mounting hole
Reserved connector
decoupling
External reset
Flash
UART communication
ESR<2ohm
22ohm near mcu to prevent from ringing
MCU
Connection to lora layer
Connection to backup_AV
Barometer
common ground to Backup_AV GND
Indicator
Buttom
USB
IMU
decoupling for VDD,VDDIO
Serial Wire Debug
